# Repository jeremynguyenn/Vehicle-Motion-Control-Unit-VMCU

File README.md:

## For security reasons, only upload photos.

# SCU ECU
 Electronic Control Unit, which handles the behaivour of the cars dynamic system while gathering all the sensor and data neccesary for operation through its inputs and communication buses.

## Features
- STM32F405VGTx Microcontroller (Cortex™-M4 Core@168mHz with FPU)
- USB For Diagnosis Operation
- 2x CAN 2.0 For its communication with the Powertrain CAN and main sensors CAN
- NEO M9N GPS modules from u-blox, for determining cars position (Posibility to drive an active Antenna)
- 9DOF IMU consisting in Accelerometer, Gyroscope and Magnetometer for accurate posting and torque algorithms
- 4 Digital Inputs (0V-24V Range)
- 4 PWM Outputs(3.3V), for servo control, including actuators
- 4 Analog Inputs (0V-3.3V) Possibility of configurable Input divider
- 4 Digital Outputs(0V-24V) High side mosfet drivers
- 2 WS2812 RGB Led Channels using integrated SPI for FS-Spain LightShow Acceleration

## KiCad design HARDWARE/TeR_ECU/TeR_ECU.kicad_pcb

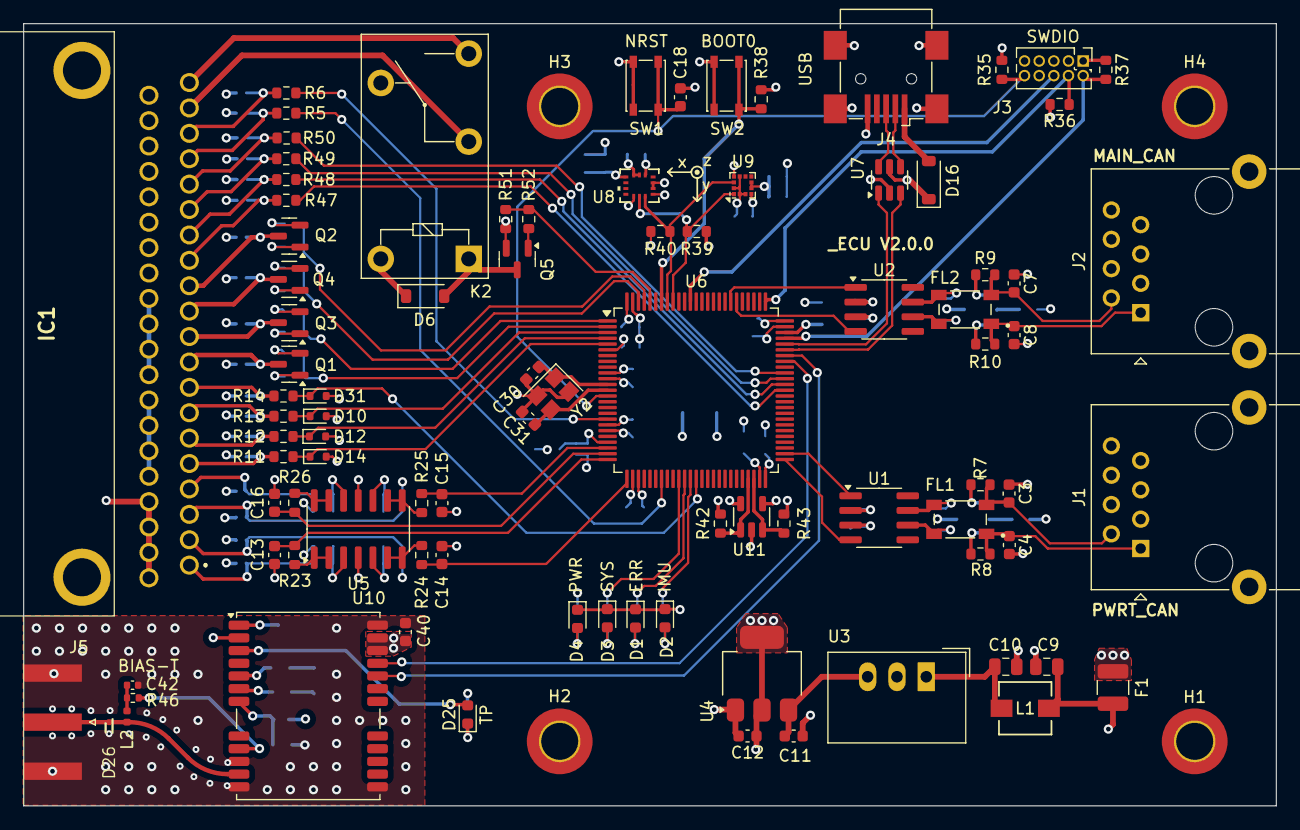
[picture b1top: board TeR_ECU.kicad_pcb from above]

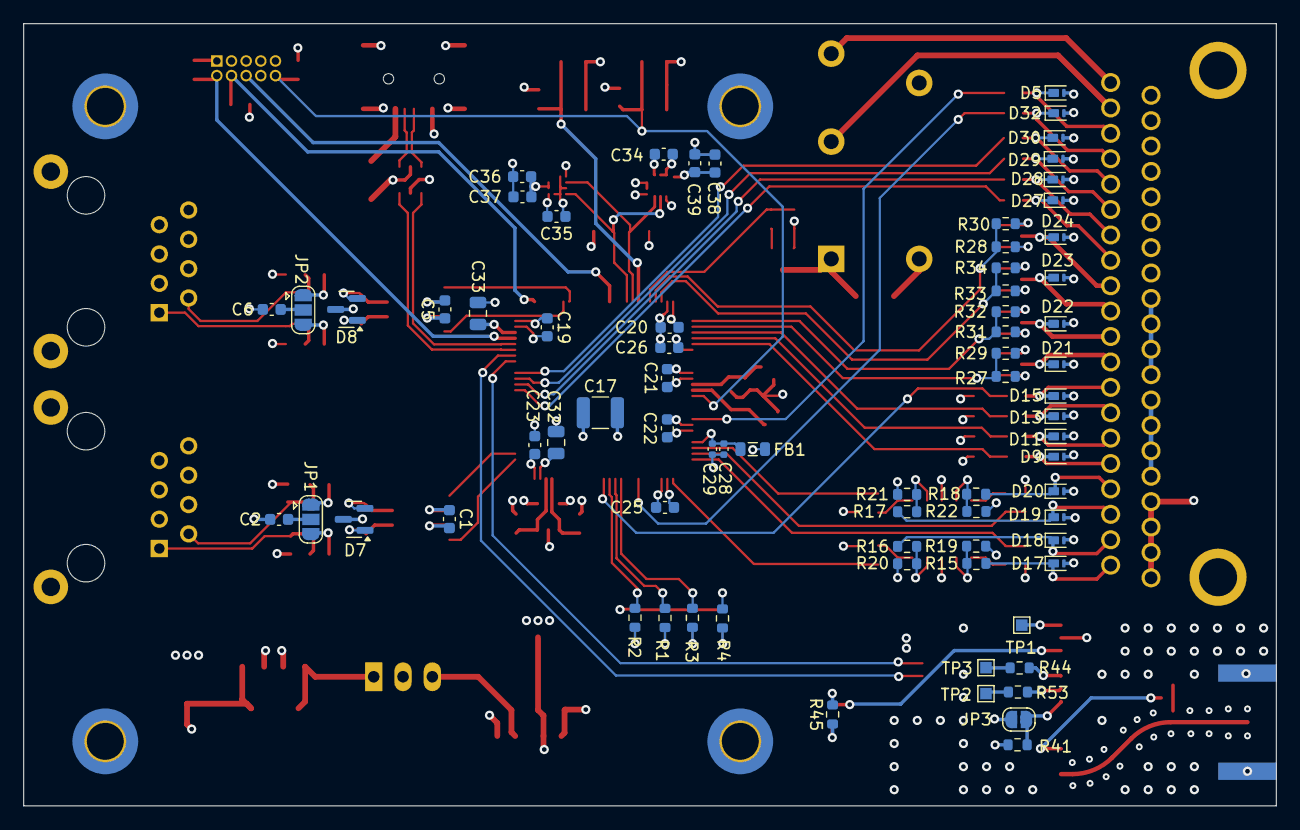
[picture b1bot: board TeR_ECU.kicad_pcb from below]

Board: 4 copper layers, 108.5 x 67.8 mm, 166 parts (73 on the bottom side), 117 nets.

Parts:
C1, C5, C34, C35, C37, C38: 100n; C_0603_1608Metric
C2, C6: 4.7nF; C_0603_1608Metric
C3, C4, C7, C8, C40: 10p; C_0603_1608Metric
C9, C10: 10 µF; C_0805_2012Metric
C11, C12, C39: 10u; C_0603_1608Metric
C13, C14, C15, C16: 20n; C_0603_1608Metric
C17: 10uF; C_1210_3225Metric
C18: 0,1uF; C_0603_1608Metric
C19, C20, C21, C22, C23, C25, C26: 100nF; C_0603_1608Metric
C28: 100nF; C_0402_1005Metric
C29: 10uF; C_0402_1005Metric
C30, C31: 30p; C_0603_1608Metric
C32, C33: 2.2uF; C_0805_2012Metric
C36: 1u; C_0603_1608Metric
C42: 10n; C_0402_1005Metric
D1: ERR; LED_0603_1608Metric
D2: IMU; LED_0603_1608Metric
D3: SYS; LED_0603_1608Metric
D4: PWR; LED_0603_1608Metric
D5, D32: PTVS7V5Z1USK; Nexperia_DSN1608-2_1.6x0.8mm
D6, D16: SS14; D_SOD-123
D7, D8: NUP2105L; SOT-23
D9, D11, D13, D15, D17, D18, D19, D20, D21, D22, D23, D24, D27, D28, D29, D30: PTVS26VZ1USK; Nexperia_DSN1608-2_1.6x0.8mm
D10, D12, D14, D31: SZMM5Z3V3T1G; D_SOD-523
D25: TPS; LED_0603_1608Metric
D26: ESD9101P2T5G; SODFL1006X40N
F1: 500mA; Fuse_1210_3225Metric
FB1: 120R; L_0805_2012Metric
FL1, FL2: ACT45B-510-2P-TL003; FIL_ACT45B-510-2P-TL003
H1, H2, H3, H4: MountingHole_Pad; MountingHole_3.2mm_M3_ISO7380_Pad_TopBottom
IC1: MX34040NF2
J1, J2: RJ45_Shielded; RJ45_Ninigi_GE
J3: DEBUG; PinHeader_2x05_P1.27mm_Vertical
J4: USB_B_Mini; USB_Mini-B_Wuerth_65100516121_Horizontal
J5: GPS_ANT; SMA_Amphenol_132289_EdgeMount
JP1, JP2: 120R Term; SolderJumper-3_P1.3mm_Open_RoundedPad1.0x1.5mm
JP3: EN_USB; SolderJumper-2_P1.3mm_Open_RoundedPad1.0x1.5mm
K2: G5Q-1; Relay_SPDT_Omron-G5Q-1
L1: TCK-141; IND_TCK-141_TRP
L2: 27nH; L_0402_1005Metric
Q1, Q2, Q3, Q4, Q5: ZXMN3F30FH; SOT-23
R1, R2, R3, R4, R7, R8, R9, R10: 120R; R_0603_1608Metric
R5, R6, R45, R47, R48, R49, R50: 100R; R_0603_1608Metric
R11, R12, R13, R14, R19, R20, R21, R22, R38, R39, R40, R42, R43, R51: 10k; R_0603_1608Metric
R15, R16, R17, R18: 0R; R_0603_1608Metric
R23, R24, R25, R26, R29, R30, R32, R34: 1K; R_0603_1608Metric
R27, R28, R31, R33, R52: 6R; R_0603_1608Metric
R35, R36, R37, R41: 100k; R_0603_1608Metric
R44, R53: 27R; R_0603_1608Metric
R46: 10R; R_0402_1005Metric
SW1: RST; SW_SPST_PTS810
SW2: BOOT0; SW_SPST_PTS810
TP1: GPS_SFBOOT; TestPoint_Pad_1.0x1.0mm
TP2: USB+; TestPoint_Pad_1.0x1.0mm
TP3: USB-; TestPoint_Pad_1.0x1.0mm
U1, U2: TCAN332; SOIC-8_3.9x4.9mm_P1.27mm
U3: TSR_1-2450; Converter_DCDC_TRACO_TSR-1_THT
U4: LM1117MP-3.3; SOT-223-3_TabPin2
U5: LM324; SOIC-14_3.9x8.7mm_P1.27mm
U6: STM32F405VGTx; LQFP-100_14x14mm_P0.5mm
U7: USBLC6-2SC6; SOT-23-6
U8: ASM330LHH; LGA-14L_2P5X3X0P83_STM-L
U9: LIS3MDL; LGA-12_2x2mm_P0.5mm
U10: NEO-M9N; ublox_NEO
U11: AT24CS02-STUM; SOT-23-5
Y2: ECS-250-20-33-CKM-TR; Crystal_SMD_3225-4Pin_3.2x2.5mm

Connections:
24_VIN: F1.1, J1.3, J1.4, J1.5, J2.3, J2.4, J2.5
+3.3V: C1.2, C5.2, C12.1, C17.1, C19.1, C20.1, C21.1, C22.1, C23.1, C25.1, C26.1, C34.1, C36.2, C37.2, C38.1, C39.2, C40.1, FB1.2, IC1.21, IC1.22, IC1.23, IC1.24, J3.1 (VTref), JP3.2 (B), R4.1, R35.1, R37.1, R39.1, R40.1, R42.1, R43.1, SW2.1 (A), U1.3 (VCC), U2.3 (VCC), U4.2 (VO), U5.4 (V+), U6.6 (VBAT), U6.11 (VDD), U6.19 (VDD), U6.28 (VDD), U6.50 (VDD), U6.75 (VDD), U6.100 (VDD), U8.2 (RES), U8.3 (RES), U8.5 (VDD_IO), U8.8 (VDD), U8.12 (CS), U9.5 (Vdd), U9.6 (Vdd_IO), U9.10 (~CS), U10.2 (D_SEL), U10.22 (V_BCKP), U10.23 (VCC), U11.4 (VCC)
+3.3VADC: C28.1, C29.1, FB1.1, U6.22 (VDDA)
+5V: C11.1, D16.1 (K), IC1.25, IC1.26, IC1.27, IC1.28, U3.3 (Vout), U4.3 (VI), U7.5 (VBUS)
+24V: C9.1, D6.1 (K), F1.2, IC1.29, IC1.30, IC1.31, IC1.32, K2.5, L1.2
/AIN0: D17.1 (K), IC1.1, R15.1
/AIN1: D18.1 (K), IC1.2, R16.1
/AIN2: D19.1 (K), IC1.3, R17.1
/AIN3: D20.1 (K), IC1.4, R18.1
/CAN_MAIN/CAN+: C3.2, FL1.2, J1.2, R7.1
/CAN_MAIN/CAN-: C4.1, FL1.1, J1.1, R8.2
/CAN_MAIN/CAN_RX: U1.4 (RXD), U6.51 (PB12)
/CAN_MAIN/CAN_TX: U1.1 (TXD), U6.52 (PB13)
/CAN_POWERTRAIN/CAN+: C7.2, FL2.2, J2.2, R9.1
/CAN_POWERTRAIN/CAN-: C8.1, FL2.1, J2.1, R10.2
/CAN_POWERTRAIN/CAN_RX: U2.4 (RXD), U6.81 (PD0)
/CAN_POWERTRAIN/CAN_TX: U2.1 (TXD), U6.82 (PD1)
/DIN0: D9.1 (K), IC1.5, R11.1
/DIN1: D11.1 (K), IC1.6, R12.1
/DIN2: D13.1 (K), IC1.7, R13.1
/DIN3: D15.1 (K), IC1.8, R14.1
/DOUT0: D21.1 (K), IC1.9, Q1.3 (D)
/DOUT1: D22.1 (K), IC1.10, Q3.3 (D)
/DOUT2: D23.1 (K), IC1.11, Q4.3 (D)
/DOUT3: D24.1 (K), IC1.12, Q2.3 (D)
/D_OUTPUTS/DO0: R27.2, R29.1, U6.2 (PE3)
/D_OUTPUTS/DO1: R31.2, R32.1, U6.1 (PE2)
/D_OUTPUTS/DO2: R33.2, R34.1, U6.98 (PE1)
/D_OUTPUTS/DO3: R28.2, R30.1, U6.97 (PE0)
/ERR_LED: R1.1, U6.36 (PB1)
/GPS/RX: U6.68 (PA9), U10.21 (RXD/SPI_MOSI)
/GPS/TX: U6.69 (PA10), U10.20 (TXD/SPI_MISO)
/IMU_LED: R2.1, U6.37 (PB2)
/INPUTS/A0: C13.1, R23.2, U6.25 (PA2)
/INPUTS/A1: C14.1, R24.2, U6.26 (PA3)
/INPUTS/A2: C15.1, R25.2, U6.23 (PA0)
/INPUTS/A3: C16.1, R26.2, U6.24 (PA1)
/INPUTS/D0: D14.1 (K), R11.2, U6.5 (PE6)
/INPUTS/D1: D12.1 (K), R12.2, U6.4 (PE5)
/INPUTS/D2: D10.1 (K), R13.2, U6.3 (PE4)
/INPUTS/D3: D31.1 (K), R14.2, U6.38 (PE7)
/LED1: D32.1 (K), IC1.17, R5.1
/LED2: D5.1 (K), IC1.18, R6.1
/LEDS/LED1_SPI: R5.2, U6.32 (PA7)
/LEDS/LED2_SPI: R6.2, U6.18 (PC3)
/MICRO_F4/BOOT0: R38.1, SW2.2 (B), U6.94 (BOOT0)
/MICRO_F4/HSE_IN: C30.1, U6.12 (PH0), Y2.1
/MICRO_F4/HSE_OUT: C31.1, U6.13 (PH1), Y2.3
/MICRO_F4/NRST: C18.1, J3.10 (~RESET), R35.2, SW1.2 (B), U6.14 (NRST)
/MICRO_F4/SCL_1: R39.2, U6.92 (PB6), U8.13 (SCL), U9.1 (SCL/SPC)
/MICRO_F4/SCL_2: R42.2, U6.47 (PB10), U11.1 (SCL)
/MICRO_F4/SC_EN: R51.2, R52.1, U6.96 (PB9)
/MICRO_F4/SDA_1: R40.2, U6.93 (PB7), U8.14 (SDA), U9.11 (SDA/SDI/SDO)
/MICRO_F4/SDA_2: R43.2, U6.48 (PB11), U11.3 (SDA)
/MICRO_F4/SWCLK: J3.4 (SWCLK/TCK), R36.1, U6.76 (PA14)
/MICRO_F4/SWDIO: J3.2 (SWDIO/TMS), R37.2, U6.72 (PA13)
/MICRO_F4/SWO: J3.6 (SWO/TDO), U6.89 (PB3)
/MICRO_F4/T3_CH1: R47.2, U6.63 (PC6)
/MICRO_F4/T3_CH2: R48.2, U6.64 (PC7)
/MICRO_F4/T3_CH3: R49.2, U6.65 (PC8)
/MICRO_F4/T3_CH4: R50.2, U6.66 (PC9)
/MICRO_F4/USB_D+: U6.71 (PA12), U7.1 (I/O1)
/MICRO_F4/USB_D-: U6.70 (PA11), U7.3 (I/O2)
/PWM0: D27.1 (K), IC1.13, R47.1
/PWM1: D28.1 (K), IC1.14, R48.1
/PWM2: D29.1 (K), IC1.15, R49.1
/PWM3: D30.1 (K), IC1.16, R50.1
/SC_IN: IC1.19, K2.2
/SC_OUT: IC1.20, K2.3
/SYS_LED: R3.1, U6.35 (PB0)
/USB/D+: J4.3 (D+), U7.6 (I/O1)
/USB/D-: J4.2 (D-), U7.4 (I/O2)
GND: C1.1, C2.2, C3.1, C4.2, C5.1, C6.2, C7.1, C8.2, C9.2, C10.2, C11.2, C12.2, C13.2, C14.2, C15.2, C16.2, C17.2, C18.2, C19.2, C20.2, C21.2, C22.2, C23.2, C25.2, C26.2, C28.2, C29.2, C30.2, C31.2, C32.2, C33.2, C34.2, C35.2, C36.1, C37.1, C38.2, C39.1, C40.2, C42.2, D1.1 (K), D2.1 (K), D3.1 (K), D4.1 (K), D5.2 (A), D7.3 (A), D8.3 (A), D9.2 (A), D10.2 (A), D11.2 (A), D12.2 (A), D13.2 (A), D14.2 (A), D15.2 (A), D17.2 (A), D18.2 (A), D19.2 (A), D20.2 (A), D21.2 (A), D22.2 (A), D23.2 (A), D24.2 (A), D26.2 (A), D27.2 (A), D28.2 (A), D29.2 (A), D30.2 (A), D31.2 (A), D32.2 (A), H1.1, H2.1, H3.1, H4.1, IC1.33, IC1.34, IC1.35, IC1.36, IC1.37, IC1.38, IC1.39, IC1.40, IC1.41, IC1.42, J1.6, J1.7, J1.8, J1.SH, J2.6, J2.7, J2.8, J2.SH, J3.3 (GND), J3.5 (GND), J3.9 (GNDDetect), J4.5 (GND), J4.6 (Shield), J5.2 (Ext), Q1.2 (S), Q2.2 (S), Q3.2 (S), Q4.2 (S), Q5.2 (S), R19.2, R20.2, R21.2, R22.2, R29.2, R30.2, R32.2, R34.2, R36.2, R38.2, R41.2, R45.2, R51.1, SW1.1 (A), U1.2 (GND), U2.2 (GND), U3.2 (GND), U4.1 (GND), U5.11 (V-), U6.10 (VSS), U6.20 (VSSA), U6.27 (VSS), U6.74 (VSS), U6.99 (VSS), U7.2 (GND), U8.1 (SDO/SA0), U8.6 (GND), U8.7 (GND), U9.2 (GND), U9.3 (GND), U9.9 (SDO/SA1), U9.12 (GND), U10.10 (GND), U10.12 (GND), U10.13 (GND), U10.24 (GND), U11.2 (GND), U11.5 (WP), Y2.2, Y2.4
unnamed: C42.1, L2.1, R46.1
unnamed: D1.2 (A), R1.2
unnamed: D2.2 (A), R2.2
unnamed: D3.2 (A), R3.2
unnamed: D4.2 (A), R4.2
unnamed: D6.2 (A), K2.1, Q5.3 (D)
unnamed: D16.2 (A), J4.1 (VBUS)
unnamed: D25.2 (A), U10.3 (TIMEPULSE)
unnamed: D25.1 (K), R45.1
unnamed: D26.1 (K), J5.1 (In), L2.2, U10.11 (RF_IN)
unnamed: JP1.1 (A), R7.2
unnamed: JP1.3 (B), R8.1
unnamed: C2.1, JP1.2 (C)
unnamed: JP2.1 (A), R9.2
unnamed: JP2.3 (B), R10.1
unnamed: C6.1, JP2.2 (C)
unnamed: JP3.1 (A), R41.1, U10.7 (VDD_USB)
unnamed: Q1.1 (G), R27.1
unnamed: Q2.1 (G), R28.1
unnamed: Q3.1 (G), R31.1
unnamed: Q4.1 (G), R33.1
unnamed: Q5.1 (G), R52.2
unnamed: R44.1, TP3.1
unnamed: R53.2, TP2.1
unnamed: D7.2 (K), FL1.3, U1.7 (CANH)
unnamed: D7.1 (K), FL1.4, U1.6 (CANL)
unnamed: D8.2 (K), FL2.3, U2.7 (CANH)
unnamed: D8.1 (K), FL2.4, U2.6 (CANL)
unnamed: C10.1, L1.1, U3.1 (Vin)
unnamed: R15.2, R19.1, U5.3 (+)
unnamed: R23.1, U5.1, U5.2 (-)
unnamed: R16.2, R20.1, U5.5 (+)
unnamed: R24.1, U5.6 (-), U5.7
unnamed: R17.2, R21.1, U5.10 (+)
unnamed: R25.1, U5.8, U5.9 (-)
unnamed: R18.2, R22.1, U5.12 (+)
unnamed: R26.1, U5.13 (-), U5.14
unnamed: C32.1, U6.49 (VCAP_1)
unnamed: C33.1, U6.73 (VCAP_2)
unnamed: C35.1, U9.4 (C1)
unnamed: R44.2, U10.5 (USB_DM)
unnamed: R53.1, U10.6 (USB_DP)
unnamed: R46.2, U10.9 (VCC_RF)
unnamed: TP1.1, U10.1 (~SAFEBOOT)

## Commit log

2025-11-30 Create LICENSE
